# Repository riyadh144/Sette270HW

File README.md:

This is the PCB for the Sette270,
It uses an ESP32 as the brains, and HX711 for the weight and some i2c IO expanssion
It is functional but I would do a couple changes before the next itteration like adding a 5V stable reference voltage

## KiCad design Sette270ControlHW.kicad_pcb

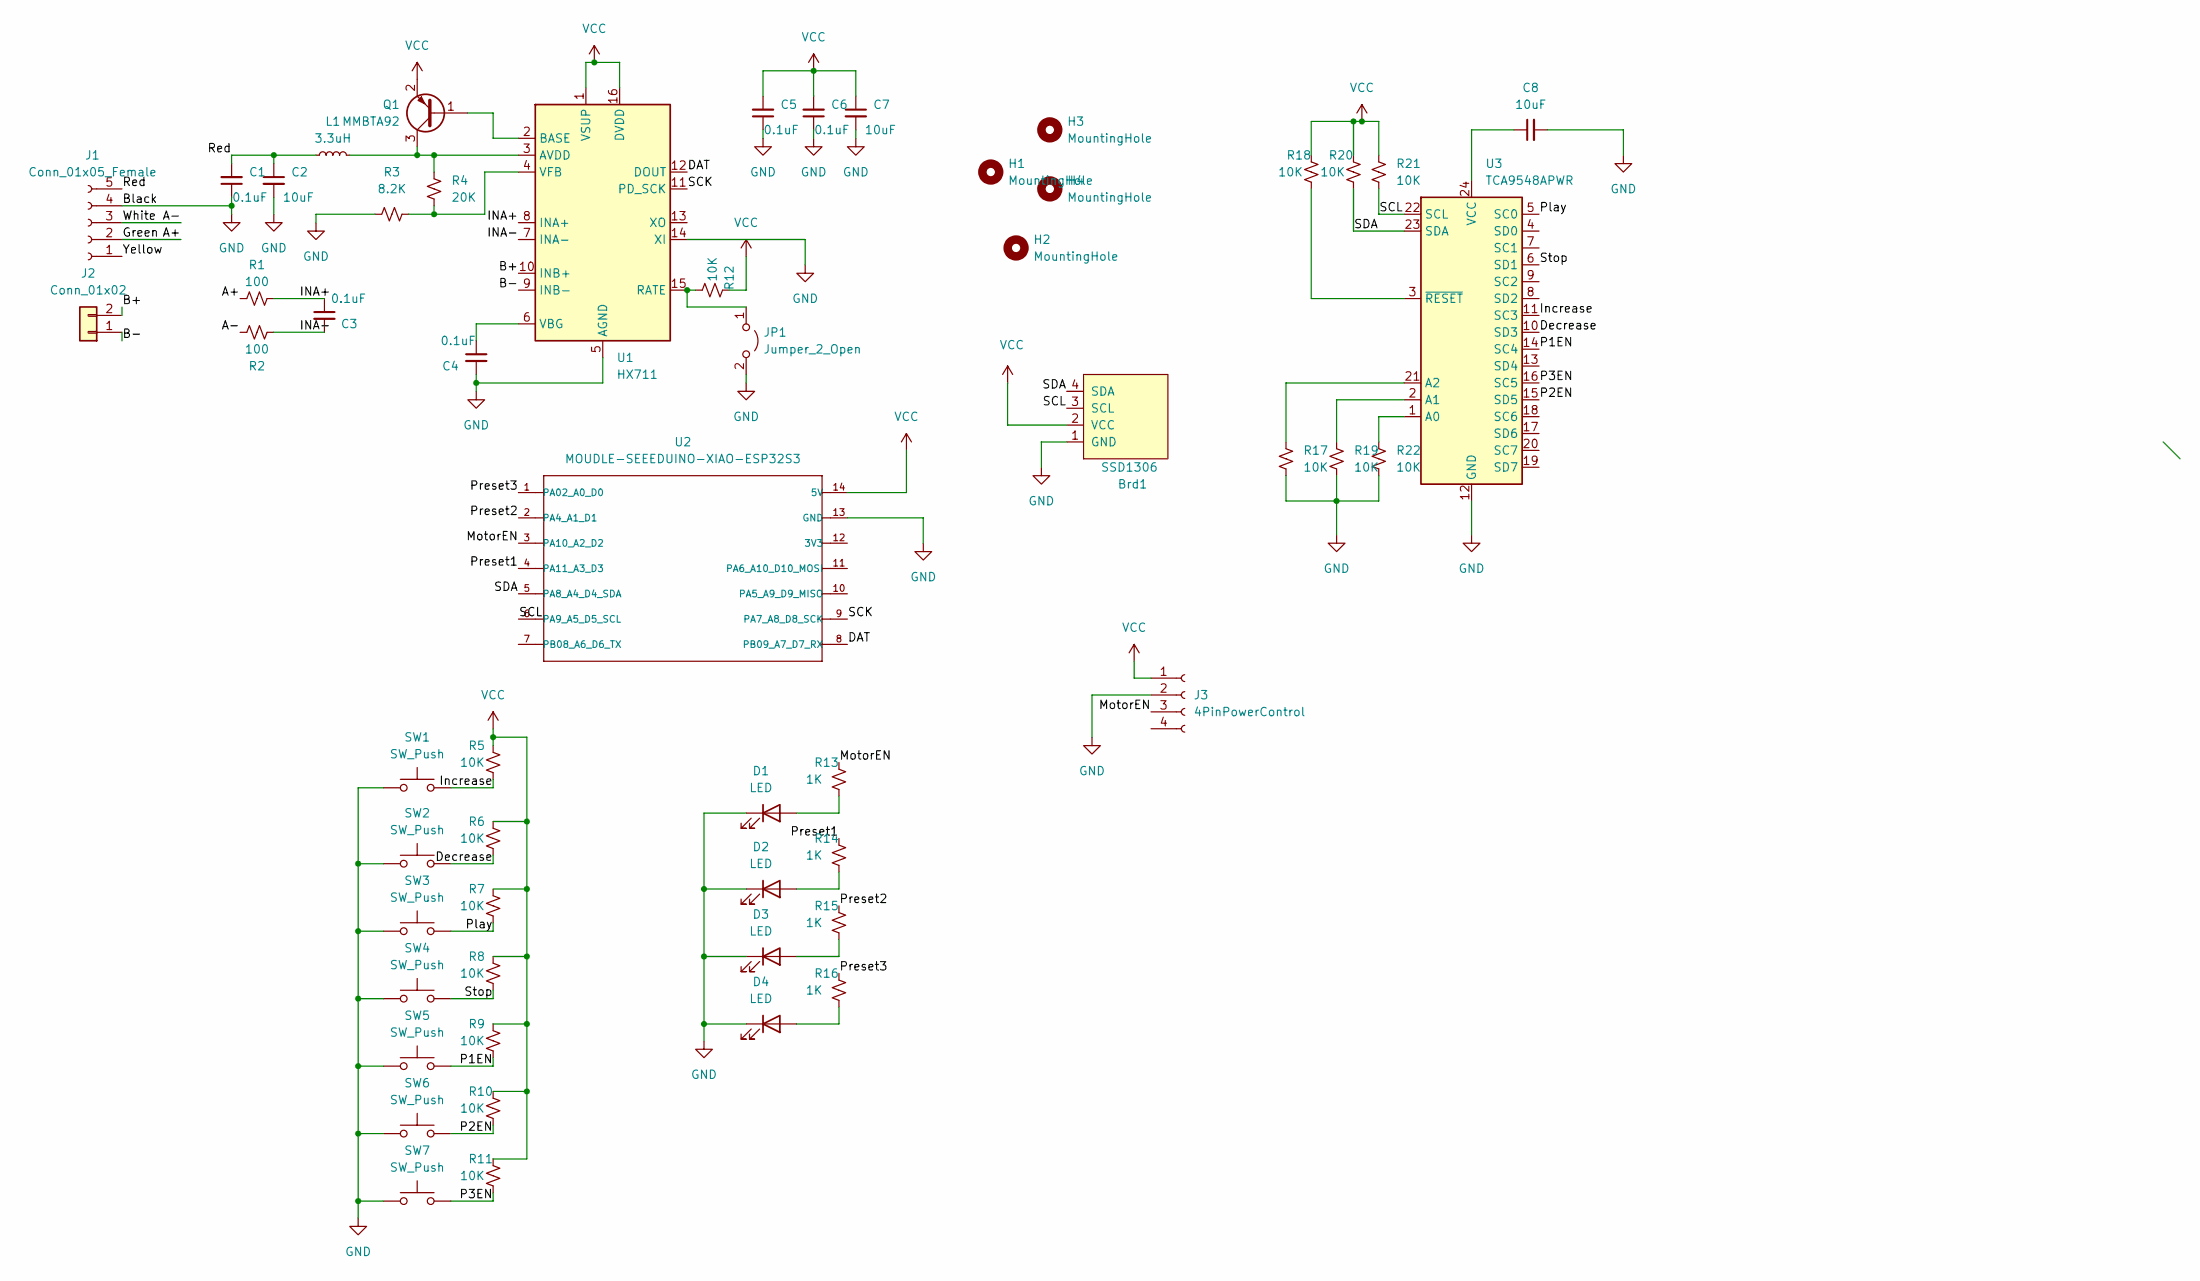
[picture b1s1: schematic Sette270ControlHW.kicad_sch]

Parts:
Brd1: SSD1306; SSD1306-0.91-OLED-4pin-128x32
C1, C3, C4, C5, C6: 0.1uF; C_0603_1608Metric_Pad1.08x0.95mm_HandSolder
C2, C7, C8: 10uF; C_0805_2012Metric_Pad1.18x1.45mm_HandSolder
D1, D2, D3, D4: LED; LED_D2.0mm_W4.8mm_H2.5mm_FlatTop
H1, H2, H3, H4: MountingHole; MountingHole_2.2mm_M2
J1: Conn_01x05_Female; PinHeader_1x05_P2.54mm_Vertical
J2: Conn_01x02; PinHeader_1x02_P1.00mm_Vertical
J3: 4PinPowerControl; PinHeader_1x04_P2.54mm_Vertical
JP1: Jumper_2_Open; PinHeader_1x02_P2.54mm_Vertical
L1: 3.3uH; L_0805_2012Metric_Pad1.05x1.20mm_HandSolder
Q1: MMBTA92; SOT-23
R1, R2: 100; R_0603_1608Metric_Pad0.98x0.95mm_HandSolder
R3: 8.2K; L_0603_1608Metric_Pad1.05x0.95mm_HandSolder
R4: 20K; L_0603_1608Metric_Pad1.05x0.95mm_HandSolder
R5, R6, R7, R8, R9, R10, R11, R12, R17, R18, R19, R20, R21, R22: 10K; R_1206_3216Metric_Pad1.30x1.75mm_HandSolder
R13, R14, R15, R16: 1K; R_0603_1608Metric_Pad0.98x0.95mm_HandSolder
SW1, SW2, SW3, SW4, SW5, SW6, SW7: SW_Push; SW_SPST_EVQQ2
U1: HX711; SOP-16_3.9x9.9mm_P1.27mm
U2: MOUDLE-SEEEDUINO-XIAO-ESP32S3; MOUDLE14P-SMD-2.54-21X17.8MM
U3: TCA9548APWR; TSSOP-24_4.4x7.8mm_P0.65mm

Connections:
/A+: J1.2, R1.1
/A-: J1.3, R2.2
/B+: J2.2, U1.10 (INB+)
/B-: J2.1, U1.9 (INB-)
/DAT: U1.12 (DOUT), U2.8 (PB09_A7_D7_RX)
/Decrease: R6.2, SW2.2, U3.10 (SD3)
/INA+: C3.1, R1.2, U1.8 (INA+)
/INA-: C3.2, R2.1, U1.7 (INA-)
/Increase: R5.2, SW1.2, U3.11 (SC3)
/MotorEN: J3.3, R13.1, U2.3 (PA10_A2_D2)
/P1EN: R9.2, SW5.2, U3.14 (SC4)
/P2EN: R10.2, SW6.2, U3.15 (SD5)
/P3EN: R11.2, SW7.2, U3.16 (SC5)
/Play: R7.2, SW3.2, U3.5 (SC0)
/Preset1: R14.1, U2.4 (PA11_A3_D3)
/Preset2: R15.1, U2.2 (PA4_A1_D1)
/Preset3: R16.1, U2.1 (PA02_A0_D0)
/Red: C1.2, C2.1, J1.5, L1.1
/SCK: U1.11 (PD_SCK), U2.9 (PA7_A8_D8_SCK)
/SCL: Brd1.3 (SCL), R21.2, U2.6 (PA9_A5_D5_SCL), U3.22 (SCL)
/SDA: Brd1.4 (SDA), R20.2, U2.5 (PA8_A4_D4_SDA), U3.23 (SDA)
/Stop: R8.2, SW4.2, U3.6 (SD1)
/Yellow: J1.1
GND: Brd1.1 (GND), C1.1, C2.2, C4.2, C5.1, C6.1, C7.2, C8.2, D1.1 (K), D2.1 (K), D3.1 (K), D4.1 (K), J1.4, J3.2, JP1.2 (B), R3.1, R17.2, R19.2, R22.2, SW1.1, SW2.1, SW3.1, SW4.1, SW5.1, SW6.1, SW7.1, U1.5 (AGND), U1.14 (XI), U2.13 (GND), U3.12 (GND)
unnamed: C4.1, U1.6 (VBG)
unnamed: C8.1, U3.24 (VCC)
unnamed: D1.2 (A), R13.2
unnamed: D2.2 (A), R14.2
unnamed: D3.2 (A), R15.2
unnamed: D4.2 (A), R16.2
unnamed: L1.2, Q1.3 (C), R4.1, U1.3 (AVDD)
unnamed: Q1.1 (B), U1.2 (BASE)
unnamed: R3.2, R4.2, U1.4 (VFB)
unnamed: JP1.1 (A), R12.2, U1.15 (RATE)
unnamed: R17.1, U3.21 (A2)
unnamed: R18.2, U3.3 (~RESET)
unnamed: R19.1, U3.2 (A1)
unnamed: R22.1, U3.1 (A0)
VCC: Brd1.2 (VCC), C5.2, C6.2, C7.1, J3.1, Q1.2 (E), R5.1, R6.1, R7.1, R8.1, R9.1, R10.1, R11.1, R12.1, R18.1, R20.1, R21.1, U1.1 (VSUP), U1.16 (DVDD), U2.14 (5V)

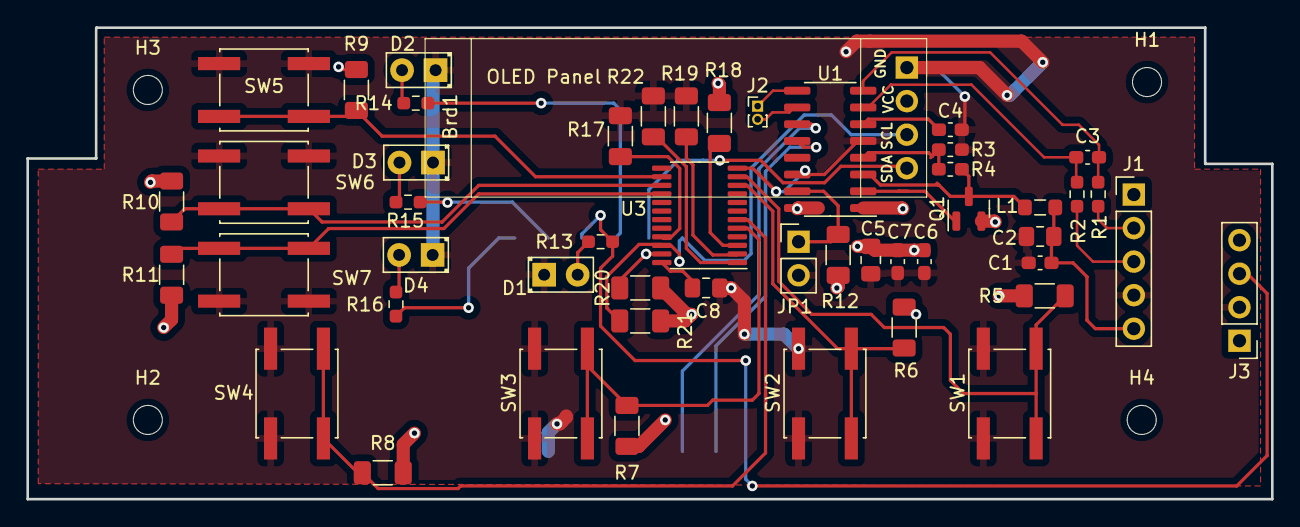
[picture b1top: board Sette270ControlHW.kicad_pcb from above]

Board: 2 copper layers, 94.3 x 35.7 mm, 55 parts (1 on the bottom side), 38 nets.
